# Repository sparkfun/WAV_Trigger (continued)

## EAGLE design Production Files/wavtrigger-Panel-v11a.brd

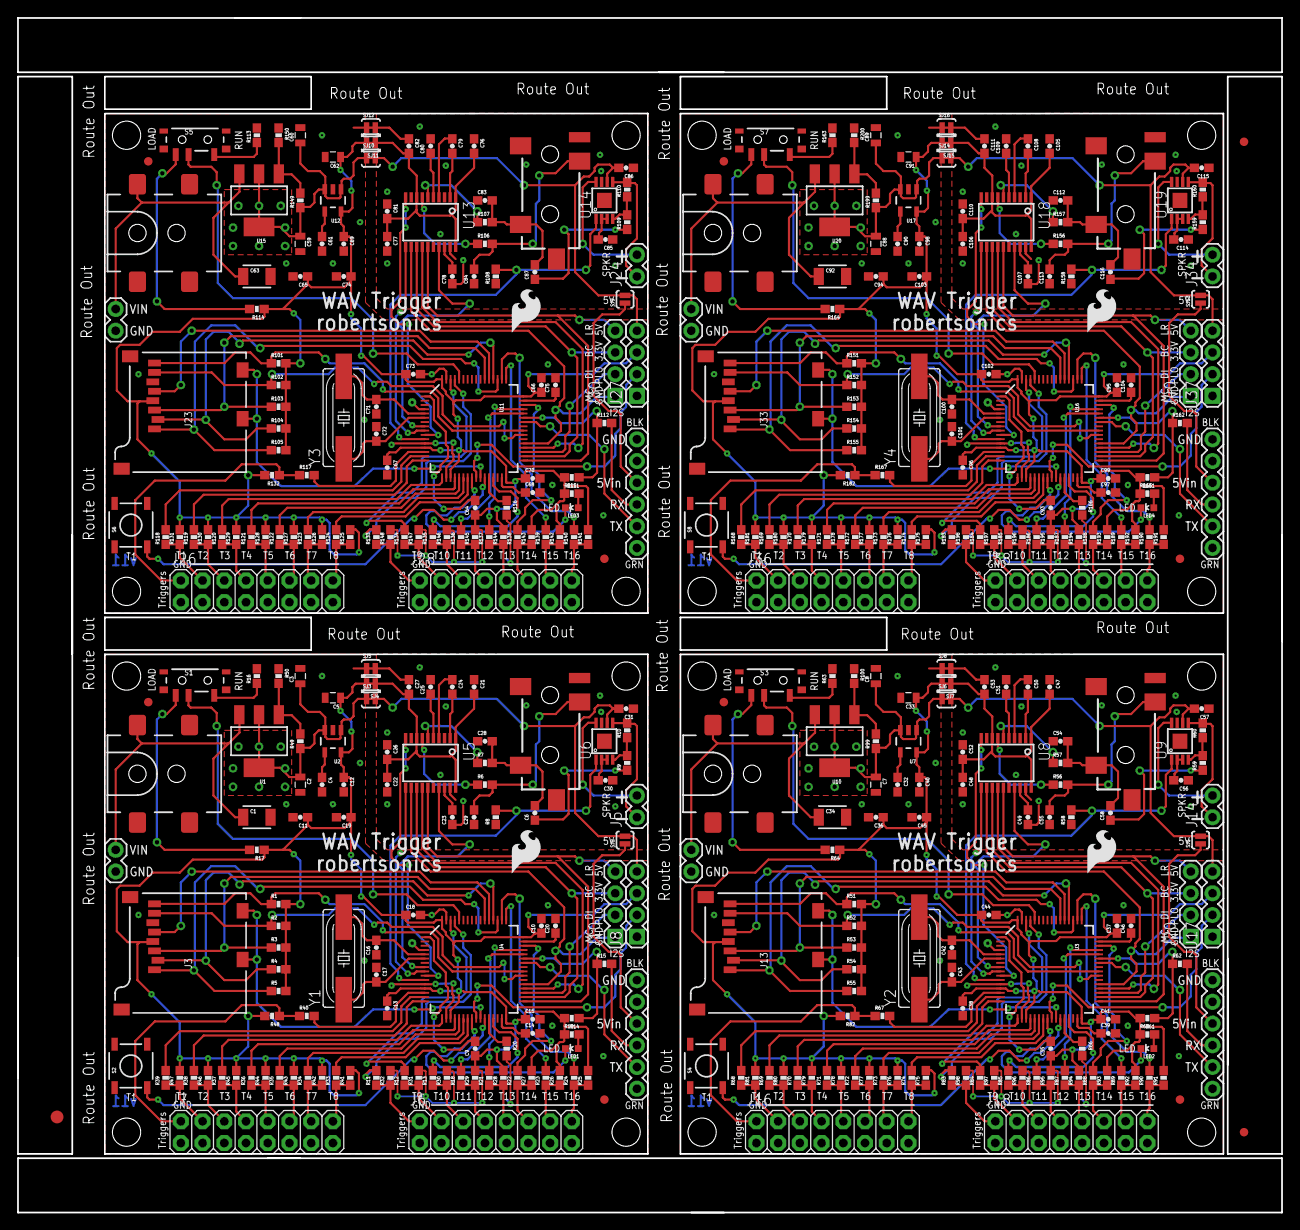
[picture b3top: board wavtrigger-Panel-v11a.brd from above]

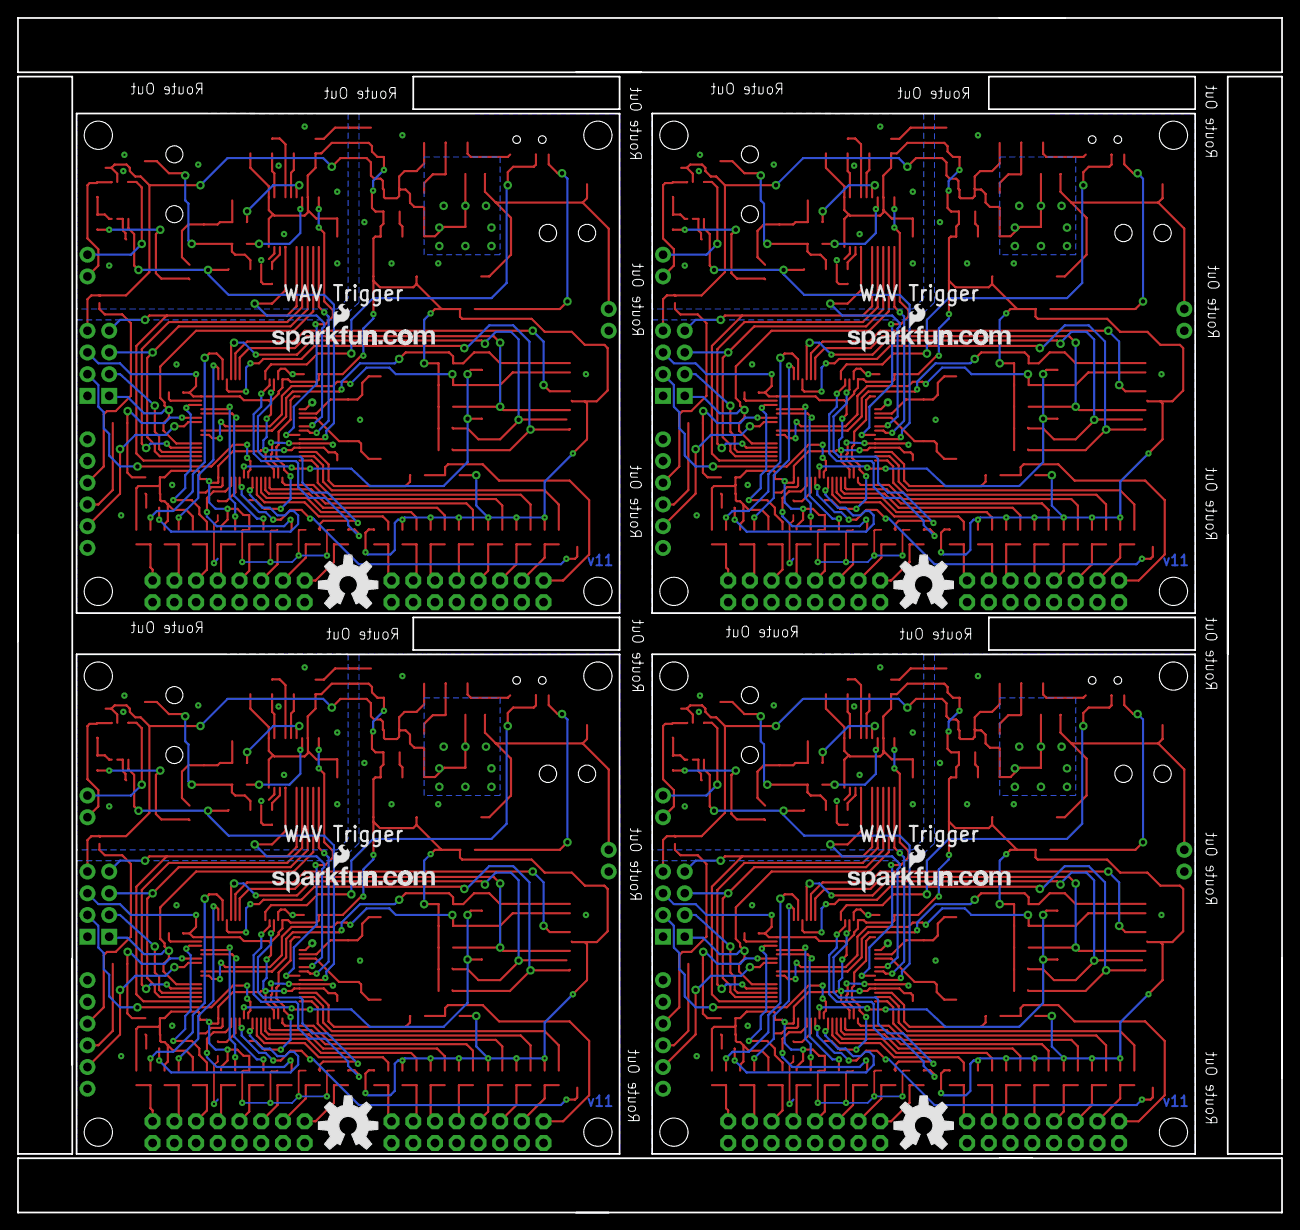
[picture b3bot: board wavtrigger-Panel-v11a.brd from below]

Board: 2 copper layers, 147.8 x 139.7 mm, 451 parts (8 on the bottom side), 340 nets.

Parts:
C1, C34, C63, C92: 10uF; 1210
C2, C7, C59, C88: 10uF; 0805
C3, C5, C8, C33, C60, C62, C89, C91: 2.2uF; 0805
C4, C9, C10, C13, C15, C18, C19, C21, C22, C23, C26, C32, C35, C37, C38, C41, C44, C45, C47, C48, C49, C52, C61, C64, C66, C67, C70, C73, C74, C76, C77, C78, C81, C90, C93, C95, C96, C99, C102, C103, C105, C106, C107, C110: 0.1uF; 0603-CAP
C6, C58, C87, C116: .39uF; 0603-CAP
C11, C30, C31, C36, C56, C57, C65, C85, C86, C94, C114, C115: 1uF; 0603-CAP
C12, C40, C69, C98: 4.7uF; 0603-CAP
C14, C20, C24, C25, C39, C46, C50, C51, C68, C75, C79, C80, C97, C104, C108, C109: 2.2uF; 0603-CAP
C16, C17, C42, C43, C71, C72, C100, C101: 33pF; 0603-CAP
C27, C53, C82, C111: 10uF; 0603-CAP
C28, C29, C54, C55, C83, C84, C112, C113: 2200pF; 0603-CAP
E$1: FIDUCIAL-1.5X3
E$13, E$14: FIDUCIAL-1X2
FID1, FID2, FID3, FID4, FID5, FID6, FID7, FID8: FIDUCIAL1X2; FIDUCIAL-1X2
J1, J11, J21, J31: 5.5x2.1mm Barrel; POWER_JACK_SMD_OVERPASTE_REDBOARD_0603
J2, J12, J22, J32: AUDIO-JACK-3.5MM-SMD
J3, J13, J23, J33: USD-SOCKETNEW; MICRO-SD-SOCKET-PP
J4, J15, J25, J35: 1X06
J5, J9, J14, J19, J24, J29, J34, J39: M02PTH; 1X02
J6, J7, J16, J18, J26, J28, J36, J38: M08X2; 2X8
J8, J10, J17, J20, J27, J30, J37, J40: 1X04
LED1, LED2, LED3, LED4: LED-0603
LOGO1, LOGO3, LOGO7, LOGO10: OSHW-LOGOL; OSHW-LOGO-L
LOGO2, LOGO5, LOGO8, LOGO11: LOGO-SFENEW; SFE-NEW-WEBLOGO
LOGO4, LOGO6, LOGO9, LOGO12: SFE_LOGO_FLAME.2_INCH; SFE_LOGO_FLAME_.2
R1, R2, R3, R4, R5, R51, R52, R53, R54, R55, R101, R102, R103, R104, R105, R151, R152, R153, R154, R155: 47K; 0603-RES
R6, R7, R56, R57, R106, R107, R156, R157: 470; 0603-RES
R8, R10, R14, R16, R17, R20, R58, R60, R61, R63, R64, R66, R108, R110, R111, R113, R114, R116, R158, R160, R161, R163, R164, R166: 10K; 0603-RES
R9, R59, R109, R159: 22K; 0603-RES
R11, R12, R13, R15, R18, R21, R22, R23, R24, R33, R34, R35, R36, R37, R38, R39, R40, R62, R67, R68, R69, R70, R71, R72, R73, R74, R83, R84, R85, R86, R87, R88, R89, R90, R112, R117, R118, R119, R120, R121, R122, R123, R124, R133, R134, R135, R136, R137, R138, R139, R140, R162, R167, R168, R169, R170, R171, R172, R173, R174, R183, R184, R185, R186, R187, R188, R189, R190: 100; 0603-RES
R19, R65, R115, R165: 330; 0603-RES
R25, R26, R27, R28, R29, R30, R31, R32, R41, R42, R43, R44, R45, R46, R47, R48, R75, R76, R77, R78, R79, R80, R81, R82, R91, R92, R93, R94, R95, R96, R97, R98, R125, R126, R127, R128, R129, R130, R131, R132, R141, R142, R143, R144, R145, R146, R147, R148, R175, R176, R177, R178, R179, R180, R181, R182, R191, R192, R193, R194, R195, R196, R197, R198: DNP; 0603-RES
R49, R99, R149, R199: 240; 0603-RES
R50, R100, R150, R200: 715; 0603-RES
S1, S3, S5, S7: SWITCH-SPST-SMD-A
S2, S4, S6, S8: SWITCH-MOMENTARY-2SMD; TACTILE_SWITCH_SMD
SJ1, SJ2, SJ9, SJ13: SOLDERJUMPERNO; SJ_2S-NO
SJ3, SJ4, SJ5, SJ6, SJ7, SJ8, SJ10, SJ11, SJ12, SJ14, SJ15, SJ16: SOLDERJUMPERTRACE; SJ_2S-TRACE
STANDOFF1, STANDOFF2, STANDOFF3, STANDOFF4, STANDOFF5, STANDOFF6, STANDOFF7, STANDOFF8, STANDOFF9, STANDOFF10, STANDOFF11, STANDOFF12, STANDOFF13, STANDOFF14, STANDOFF15, STANDOFF16: STAND-OFF
TP1, TP2, TP3, TP4: TEST-POINTTP_15TH_THRU; TP_15TH
U1, U10, U15, U20: SOT223
U2, U7, U12, U17: MIC5323-3.3; SOT23-5
U3, U4, U11, U16: STM32F405RG; TQFP64
U5, U8, U13, U18: PCM5100; PW_R-PDSO-G20
U6, U9, U14, U19: LM4990; S-PDSO-G08
Y1, Y2, Y3, Y4: 8MHz; HC49UP

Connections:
+5V: C2.1, C3.1, C31.2, J8.4, R49.1, SJ2.2, SJ3.1, SJ3.2, U1.2, U1.4, U2.1, U2.3, U6.6
+5V1: C7.1, C8.1, C57.2, J17.4, R99.1, SJ1.2, SJ6.1, SJ6.2, U7.1, U7.3, U9.6, U10.2, U10.4
+5V2: C59.1, C60.1, C86.2, J27.4, R149.1, SJ9.2, SJ10.1, SJ10.2, U12.1, U12.3, U14.6, U15.2, U15.4
+5V3: C88.1, C89.1, C115.2, J37.4, R199.1, SJ13.2, SJ14.1, SJ14.2, U17.1, U17.3, U19.6, U20.2, U20.4
AMPENA: R8.2, U4.11, U6.1
AMPENA1: R58.2, U3.11, U9.1
AMPENA2: R108.2, U11.11, U14.1
AMPENA3: R158.2, U16.11, U19.1
BOOT0: S1.2, U4.60
BOOT1: S3.2, U3.60
BOOT2: S5.2, U11.60
BOOT3: S7.2, U16.60
BUTTON: S2.3, U4.27
BUTTON1: S4.3, U3.27
BUTTON2: S6.3, U11.27
BUTTON3: S8.3, U16.27
DEMP: U4.10, U5.10
DEMP1: U3.10, U8.10
DEMP2: U11.10, U13.10
DEMP3: U16.10, U18.10
FILTER: U4.9, U5.11
FILTER1: U3.9, U8.11
FILTER2: U11.9, U13.11
FILTER3: U16.9, U18.11
GND: C1.2, C2.2, C3.2, C4.2, C5.2, C10.2, C11.2, C12.2, C13.2, C14.2, C15.2, C16.1, C17.1, C18.2, C19.2, C20.2, C21.1, C22.2, C23.1, C25.2, C26.1, C27.1, C28.1, C29.1, C30.1, C31.1, J1.GND, J1.P$4, J2.SLEEVE, J3.6, J3.GND1, J3.GND3, J4.1, J6.1, J6.3, J6.5, J6.7, J6.9, J6.11, J6.13, J6.15, J7.1, J7.3, J7.5, J7.7, J7.9, J7.11, J7.13, J7.15, J8.1, J9.1, R8.1, R16.2, R20.2, R50.1, S2.1, SJ5.1, SJ5.2, U2.2, U4.12, U4.18, U4.63, U5.3, U5.9, U5.16, U5.19, U6.7
GND1: C7.2, C8.2, C32.2, C33.2, C34.2, C36.2, C37.2, C38.2, C39.2, C40.2, C41.2, C42.1, C43.1, C44.2, C45.2, C46.2, C47.1, C48.2, C49.1, C51.2, C52.1, C53.1, C54.1, C55.1, C56.1, C57.1, J11.GND, J11.P$4, J12.SLEEVE, J13.6, J13.GND1, J13.GND3, J15.1, J16.1, J16.3, J16.5, J16.7, J16.9, J16.11, J16.13, J16.15, J17.1, J18.1, J18.3, J18.5, J18.7, J18.9, J18.11, J18.13, J18.15, J19.1, R58.1, R63.2, R66.2, R100.1, S4.1, SJ8.1, SJ8.2, U3.12, U3.18, U3.63, U7.2, U8.3, U8.9, U8.16, U8.19, U9.7
GND2: C59.2, C60.2, C61.2, C62.2, C63.2, C65.2, C66.2, C67.2, C68.2, C69.2, C70.2, C71.1, C72.1, C73.2, C74.2, C75.2, C76.1, C77.2, C78.1, C80.2, C81.1, C82.1, C83.1, C84.1, C85.1, C86.1, J21.GND, J21.P$4, J22.SLEEVE, J23.6, J23.GND1, J23.GND3, J25.1, J26.1, J26.3, J26.5, J26.7, J26.9, J26.11, J26.13, J26.15, J27.1, J28.1, J28.3, J28.5, J28.7, J28.9, J28.11, J28.13, J28.15, J29.1, R108.1, R113.2, R116.2, R150.1, S6.1, SJ12.1, SJ12.2, U11.12, U11.18, U11.63, U12.2, U13.3, U13.9, U13.16, U13.19, U14.7
GND3: C88.2, C89.2, C90.2, C91.2, C92.2, C94.2, C95.2, C96.2, C97.2, C98.2, C99.2, C100.1, C101.1, C102.2, C103.2, C104.2, C105.1, C106.2, C107.1, C109.2, C110.1, C111.1, C112.1, C113.1, C114.1, C115.1, J31.GND, J31.P$4, J32.SLEEVE, J33.6, J33.GND1, J33.GND3, J35.1, J36.1, J36.3, J36.5, J36.7, J36.9, J36.11, J36.13, J36.15, J37.1, J38.1, J38.3, J38.5, J38.7, J38.9, J38.11, J38.13, J38.15, J39.1, R158.1, R163.2, R166.2, R200.1, S8.1, SJ16.1, SJ16.2, U16.12, U16.18, U16.63, U17.2, U18.3, U18.9, U18.16, U18.19, U19.7
I2S_BCLK: J10.3, U4.34, U5.13
I2S_BCLK1: J20.3, U3.34, U8.13
I2S_BCLK2: J30.3, U11.34, U13.13
I2S_BCLK3: J40.3, U16.34, U18.13
I2S_DI: J10.2, U4.35
I2S_DI1: J20.2, U3.35
I2S_DI2: J30.2, U11.35
I2S_DI3: J40.2, U16.35
I2S_DOUT: U4.36, U5.14
I2S_DOUT1: U3.36, U8.14
I2S_DOUT2: U11.36, U13.14
I2S_DOUT3: U16.36, U18.14
I2S_LRCK: J10.4, U4.33, U5.15
I2S_LRCK1: J20.4, U3.33, U8.15
I2S_LRCK2: J30.4, U11.33, U13.15
I2S_LRCK3: J40.4, U16.33, U18.15
I2S_MCLK: J10.1, U4.37, U5.12
I2S_MCLK1: J20.1, U3.37, U8.12
I2S_MCLK2: J30.1, U11.37, U13.12
I2S_MCLK3: J40.1, U16.37, U18.12
LED1: LED1.C, U4.24
LED2: LED2.C, U3.24
LED3: LED3.C, U11.24
LED4: LED4.C, U16.24
LOUTL: C6.2, C28.2, J2.TIP, R7.2
LOUTL1: C54.2, C58.2, J12.TIP, R57.2
LOUTL2: C83.2, C87.2, J22.TIP, R107.2
LOUTL3: C112.2, C116.2, J32.TIP, R157.2
LOUTR: C29.2, J2.RING, R6.2
LOUTR1: C55.2, J12.RING, R56.2
LOUTR2: C84.2, J22.RING, R106.2
LOUTR3: C113.2, J32.RING, R156.2
MUTE: U4.8, U5.17
MUTE1: U3.8, U8.17
MUTE2: U11.8, U13.17
MUTE3: U16.8, U18.17
unnamed: J6.2, R11.1, R32.1
unnamed: C4.1, U2.4
unnamed: C9.2, U4.1
unnamed: C14.1, U4.31
unnamed: C16.2, U4.5, Y1.2
unnamed: C17.2, U4.6, Y1.1
unnamed: R16.1, S1.3
unnamed: C20.1, U4.47
unnamed: J4.4, R15.2
unnamed: R17.2, S1.1
unnamed: LED1.A, R19.2
unnamed: R20.1, U4.28
unnamed: R49.2, R50.2, U1.1
unnamed: C23.2, U5.18
unnamed: R6.1, U5.7
unnamed: C24.2, U5.2
unnamed: C24.1, U5.4
unnamed: C25.1, U5.5
unnamed: R7.1, U5.6
unnamed: C30.2, U6.2, U6.3
unnamed: C6.1, R9.1
unnamed: TP1.P$1, U4.4
unnamed: J6.4, R12.1, R31.1
unnamed: J6.6, R13.1, R30.1
unnamed: J6.8, R18.1, R29.1
unnamed: J6.10, R21.1, R28.1
unnamed: J6.12, R22.1, R27.1
unnamed: J6.14, R23.1, R26.1
unnamed: R9.2, R10.1, U6.4
unnamed: J6.16, R24.1, R25.1
unnamed: C32.1, U7.4
unnamed: J4.3, SJ2.1
unnamed: C35.2, U3.1
unnamed: C39.1, U3.31
unnamed: J7.2, R40.1, R48.1
unnamed: J7.4, R39.1, R47.1
unnamed: J7.6, R38.1, R46.1
unnamed: J7.8, R37.1, R45.1
unnamed: J7.10, R36.1, R44.1
unnamed: J7.12, R35.1, R43.1
unnamed: J7.14, R34.1, R42.1
unnamed: J7.16, R33.1, R41.1
unnamed: C42.2, U3.5, Y2.2
unnamed: C43.2, U3.6, Y2.1
unnamed: C46.1, U3.47
unnamed: C49.2, U8.18
unnamed: C50.2, U8.2
unnamed: C50.1, U8.4
unnamed: C51.1, U8.5
unnamed: R56.1, U8.7
unnamed: R57.1, U8.6
unnamed: C56.2, U9.2, U9.3
unnamed: R59.2, R60.1, U9.4
unnamed: J15.4, R62.2
unnamed: R63.1, S3.3
unnamed: R64.2, S3.1
unnamed: LED2.A, R65.2
unnamed: R66.1, U3.28
unnamed: J15.3, SJ1.1
unnamed: J16.2, R67.1, R82.1
unnamed: J16.4, R68.1, R81.1
unnamed: J16.6, R69.1, R80.1
unnamed: J16.8, R70.1, R79.1
unnamed: J16.10, R71.1, R78.1
unnamed: J16.12, R72.1, R77.1
unnamed: J16.14, R73.1, R76.1
unnamed: J16.16, R74.1, R75.1
unnamed: J18.2, R83.1, R98.1
unnamed: J18.4, R84.1, R97.1
unnamed: J18.6, R85.1, R96.1
unnamed: J18.8, R86.1, R95.1
unnamed: J18.10, R87.1, R94.1
unnamed: J18.12, R88.1, R93.1
unnamed: J18.14, R89.1, R92.1
unnamed: J18.16, R90.1, R91.1
unnamed: R99.2, R100.2, U10.1
unnamed: C58.1, R59.1
unnamed: TP2.P$1, U3.4
unnamed: C61.1, U12.4
unnamed: C64.2, U11.1
unnamed: C68.1, U11.31
unnamed: C71.2, U11.5, Y3.2
unnamed: C72.2, U11.6, Y3.1
unnamed: C75.1, U11.47
unnamed: C78.2, U13.18
unnamed: C79.2, U13.2
unnamed: C79.1, U13.4
unnamed: C80.1, U13.5
unnamed: R106.1, U13.7
unnamed: R107.1, U13.6
unnamed: C85.2, U14.2, U14.3
unnamed: R109.2, R110.1, U14.4
unnamed: J25.4, R112.2
unnamed: R113.1, S5.3
unnamed: R114.2, S5.1
unnamed: LED3.A, R115.2
unnamed: R116.1, U11.28
unnamed: J25.3, SJ9.1
unnamed: J26.2, R117.1, R132.1
unnamed: J26.4, R118.1, R131.1
unnamed: J26.6, R119.1, R130.1
unnamed: J26.8, R120.1, R129.1
unnamed: J26.10, R121.1, R128.1
unnamed: J26.12, R122.1, R127.1
unnamed: J26.14, R123.1, R126.1
unnamed: J26.16, R124.1, R125.1
unnamed: J28.2, R133.1, R148.1
unnamed: J28.4, R134.1, R147.1
unnamed: J28.6, R135.1, R146.1
unnamed: J28.8, R136.1, R145.1
unnamed: J28.10, R137.1, R144.1
unnamed: J28.12, R138.1, R143.1
unnamed: J28.14, R139.1, R142.1
unnamed: J28.16, R140.1, R141.1
unnamed: R149.2, R150.2, U15.1
unnamed: C87.1, R109.1
unnamed: TP3.P$1, U11.4
unnamed: C90.1, U17.4
unnamed: C93.2, U16.1
unnamed: C97.1, U16.31
unnamed: C100.2, U16.5, Y4.2
unnamed: C101.2, U16.6, Y4.1
unnamed: C104.1, U16.47
unnamed: C107.2, U18.18
unnamed: C108.2, U18.2
unnamed: C108.1, U18.4
unnamed: C109.1, U18.5
unnamed: R156.1, U18.7
unnamed: R157.1, U18.6
unnamed: C114.2, U19.2, U19.3
unnamed: R159.2, R160.1, U19.4
unnamed: J35.4, R162.2
unnamed: R163.1, S7.3
unnamed: R164.2, S7.1
unnamed: LED4.A, R165.2
unnamed: R166.1, U16.28
unnamed: J35.3, SJ13.1
unnamed: J36.2, R167.1, R182.1
unnamed: J36.4, R168.1, R181.1
unnamed: J36.6, R169.1, R180.1
unnamed: J36.8, R170.1, R179.1
unnamed: J36.10, R171.1, R178.1
unnamed: J36.12, R172.1, R177.1
unnamed: J36.14, R173.1, R176.1
unnamed: J36.16, R174.1, R175.1
unnamed: J38.2, R183.1, R198.1
unnamed: J38.4, R184.1, R197.1
unnamed: J38.6, R185.1, R196.1
unnamed: J38.8, R186.1, R195.1
unnamed: J38.10, R187.1, R194.1
unnamed: J38.12, R188.1, R193.1
unnamed: J38.14, R189.1, R192.1
unnamed: J38.16, R190.1, R191.1
unnamed: R199.2, R200.2, U20.1
unnamed: C116.1, R159.1
unnamed: TP4.P$1, U16.4
PLAYOUT: J8.2, U4.25
PLAYOUT1: J17.2, U3.25
PLAYOUT2: J27.2, U11.25
PLAYOUT3: J37.2, U16.25
RXD: R14.1, R15.1, U4.43
RXD1: R61.1, R62.1, U3.43
RXD2: R111.1, R112.1, U11.43
RXD3: R161.1, R162.1, U16.43
SD_CD: J3.CD1, J3.CD2, U4.26
SD_CD1: J13.CD1, J13.CD2, U3.26
SD_CD2: J23.CD1, J23.CD2, U11.26
SD_CD3: J33.CD1, J33.CD2, U16.26
SD_CK: J3.5, U4.53
SD_CK1: J13.5, U3.53
SD_CK2: J23.5, U11.53
SD_CK3: J33.5, U16.53
SD_CMD: J3.3, R3.1, U4.54
SD_CMD1: J13.3, R53.1, U3.54
SD_CMD2: J23.3, R103.1, U11.54
SD_CMD3: J33.3, R153.1, U16.54
SD_D0: J3.7, R2.1, U4.39
SD_D1: J3.8, R1.1, U4.40
SD_D2: J3.1, R5.1, U4.51
SD_D3: J3.2, R4.1, U4.52
SD_D4: J13.8, R51.1, U3.40
SD_D5: J13.7, R52.1, U3.39
SD_D6: J13.2, R54.1, U3.52
SD_D7: J13.1, R55.1, U3.51
SD_D8: J23.8, R101.1, U11.40
SD_D9: J23.7, R102.1, U11.39
SD_D10: J23.2, R104.1, U11.52
SD_D11: J23.1, R105.1, U11.51
SD_D12: J33.8, R151.1, U16.40
SD_D13: J33.7, R152.1, U16.39
SD_D14: J33.2, R154.1, U16.52
SD_D15: J33.1, R155.1, U16.51
SPKR+: J5.2, U6.8
SPKR+1: J14.2, U9.8
SPKR+2: J24.2, U14.8
SPKR+3: J34.2, U19.8
SPKR-: J5.1, R10.2, U6.5
SPKR-1: J14.1, R60.2, U9.5
SPKR-2: J24.1, R110.2, U14.5
SPKR-3: J34.1, R160.2, U19.5
TRIG00: R40.2, U4.14
TRIG01: R39.2, U4.15
TRIG02: R38.2, U4.16
TRIG03: R37.2, U4.17
TRIG04: R36.2, U4.20
TRIG05: R35.2, U4.21
TRIG06: R34.2, U4.22
TRIG07: R33.2, U4.23
TRIG08: R11.2, U4.61
TRIG09: R12.2, U4.62
TRIG10: R13.2, U4.29
TRIG11: R18.2, U4.44
TRIG12: R21.2, U4.45
TRIG13: R22.2, U4.46
TRIG14: R23.2, U4.49
TRIG15: R24.2, U4.50
TRIG16: R67.2, U3.14
TRIG17: R68.2, U3.15
TRIG18: R69.2, U3.16
TRIG19: R70.2, U3.17
TRIG20: R71.2, U3.20
TRIG21: R72.2, U3.21
TRIG22: R73.2, U3.22
TRIG23: R74.2, U3.23
TRIG24: R83.2, U3.61
TRIG25: R84.2, U3.62
TRIG26: R85.2, U3.29
TRIG27: R86.2, U3.44
TRIG28: R87.2, U3.45
TRIG29: R88.2, U3.46
TRIG30: R89.2, U3.49
TRIG31: R90.2, U3.50
TRIG32: R117.2, U11.14
TRIG33: R118.2, U11.15
TRIG34: R119.2, U11.16
TRIG35: R120.2, U11.17
TRIG36: R121.2, U11.20
TRIG37: R122.2, U11.21
TRIG38: R123.2, U11.22
TRIG39: R124.2, U11.23
TRIG40: R133.2, U11.61
TRIG41: R134.2, U11.62
TRIG42: R135.2, U11.29
TRIG43: R136.2, U11.44
TRIG44: R137.2, U11.45
TRIG45: R138.2, U11.46
TRIG46: R139.2, U11.49
TRIG47: R140.2, U11.50
TRIG48: R167.2, U16.14
TRIG49: R168.2, U16.15
TRIG50: R169.2, U16.16
TRIG51: R170.2, U16.17
TRIG52: R171.2, U16.20
TRIG53: R172.2, U16.21
TRIG54: R173.2, U16.22
TRIG55: R174.2, U16.23
TRIG56: R183.2, U16.61
TRIG57: R184.2, U16.62
TRIG58: R185.2, U16.29
TRIG59: R186.2, U16.44
TRIG60: R187.2, U16.45
TRIG61: R188.2, U16.46
TRIG62: R189.2, U16.49
TRIG63: R190.2, U16.50
TXD: J4.5, U4.42
TXD1: J15.5, U3.42
TXD2: J25.5, U11.42
TXD3: J35.5, U16.42
VCC: C5.1, C9.1, C10.1, C11.1, C12.1, C13.1, C15.1, C18.1, C19.1, C21.2, C22.1, C26.2, C27.2, J3.4, J8.3, R1.2, R2.2, R3.2, R4.2, R5.2, R14.2, R17.1, R19.1, R25.2, R26.2, R27.2, R28.2, R29.2, R30.2, R31.2, R32.2, R41.2, R42.2, R43.2, R44.2, R45.2, R46.2, R47.2, R48.2, SJ4.1, SJ4.2, U2.5, U4.13, U4.19, U4.32, U4.48, U4.64, U5.1, U5.8, U5.20
VCC1: C33.1, C35.1, C36.1, C37.1, C38.1, C40.1, C41.1, C44.1, C45.1, C47.2, C48.1, C52.2, C53.2, J13.4, J17.3, R51.2, R52.2, R53.2, R54.2, R55.2, R61.2, R64.1, R65.1, R75.2, R76.2, R77.2, R78.2, R79.2, R80.2, R81.2, R82.2, R91.2, R92.2, R93.2, R94.2, R95.2, R96.2, R97.2, R98.2, SJ7.1, SJ7.2, U3.13, U3.19, U3.32, U3.48, U3.64, U7.5, U8.1, U8.8, U8.20
VCC2: C62.1, C64.1, C65.1, C66.1, C67.1, C69.1, C70.1, C73.1, C74.1, C76.2, C77.1, C81.2, C82.2, J23.4, J27.3, R101.2, R102.2, R103.2, R104.2, R105.2, R111.2, R114.1, R115.1, R125.2, R126.2, R127.2, R128.2, R129.2, R130.2, R131.2, R132.2, R141.2, R142.2, R143.2, R144.2, R145.2, R146.2, R147.2, R148.2, SJ11.1, SJ11.2, U11.13, U11.19, U11.32, U11.48, U11.64, U12.5, U13.1, U13.8, U13.20
VCC3: C91.1, C93.1, C94.1, C95.1, C96.1, C98.1, C99.1, C102.1, C103.1, C105.2, C106.1, C110.2, C111.2, J33.4, J37.3, R151.2, R152.2, R153.2, R154.2, R155.2, R161.2, R164.1, R165.1, R175.2, R176.2, R177.2, R178.2, R179.2, R180.2, R181.2, R182.2, R191.2, R192.2, R193.2, R194.2, R195.2, R196.2, R197.2, R198.2, SJ15.1, SJ15.2, U16.13, U16.19, U16.32, U16.48, U16.64, U17.5, U18.1, U18.8, U18.20
VIN: C1.1, J1.VIN0, J9.2, U1.3
VIN1: C34.1, J11.VIN0, J19.2, U10.3
VIN2: C63.1, J21.VIN0, J29.2, U15.3
VIN3: C92.1, J31.VIN0, J39.2, U20.3

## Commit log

2013-04-04 first
2013-04-04 added Jamie's project files
2013-04-09 v010
    files sent to Jamie
2013-07-18 v31, ready for review
2013-07-23 v31, ready for protos, now dubbed 'pro' version
2013-07-25 changed version mark back to v30
2013-09-20 v04 hardware files
2013-10-02 Next round of protos ready for order, v04
2013-11-01 v10 red ready
2013-11-04 v10, frame update
2013-11-05 Added local micro fiducials
2013-11-05 Created Panel
2014-01-16 updated v10, changed C24-25 values to improve audio quality
2014-01-30 Updating README
2014-04-25 v11 rev for review
2014-04-28 v11 ready for protos
2014-06-16 updated silk on v11 rev, ready for reds
2014-06-19 added regular fiducial, changed barrel jack FP
2014-06-20 created panel v11
    deleted panel v10
2014-06-30 changed micro fid to regular
    also deleted "wrong" panel, re-doing it
2014-06-30 re-created panel v10
2014-06-30 Reverting back to panel v10
2014-07-01 re-did panel v11 for GP
2025-06-27 Update README.md
    Updating link
